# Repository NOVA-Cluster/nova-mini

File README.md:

# Nova Mini Project Suite

## Overview
The Nova Mini project suite consists of two main components that work together to create an interactive memory game experience:

1. Nova Mini (Receiver)
2. Nova Mini Remote (Sender)

These devices communicate wirelessly using ESP-NOW protocol to create an engaging, interactive game experience based on the classic Simon memory game.

## Components

### Nova Mini (Receiver)
The main game controller that:
- Handles core game logic and state management
- Controls LED patterns and audio feedback
- Processes player inputs
- Manages game progression through levels and rounds
- Provides hardware-level control and feedback

### Nova Mini Remote (Sender)
The user interface controller that:
- Initiates game commands and controls
- Sends instructions to the Nova Mini receiver
- Provides real-time game state updates
- Offers enhanced game mode features
- Enables remote gameplay control

## Technical Stack

### Hardware
Both devices are built on the ESP32 platform, featuring:
- ESP32 microcontroller
- LED indicators for visual feedback
- Push buttons for user input
- Buzzer for audio feedback
- Custom PCB design

### Software
Built using modern embedded development tools and frameworks:
- PlatformIO development environment
- Arduino framework for ESP32
- ESP-NOW protocol for wireless communication
- Custom libraries:
  - ESPUI for web interface
  - AsyncWebServer for configuration
  - MIDI Library for audio control
  - ArduinoJson for data serialization
  - OneButton for enhanced button control

## Communication

The devices use ESP-NOW, a connectionless wireless communication protocol that enables:
- Low-latency communication
- Peer-to-peer data exchange
- Efficient power usage
- Reliable message delivery

## Game Features

- Multiple difficulty levels and progressive rounds
- Real-time LED and audio feedback
- Enhanced state management with stages:
  - Sequence Generation
  - Input Collection
  - Verification
  - Round Transition
  - Game Win/Loss states
- Remote control capabilities
- Cheat mode for testing

## Setup and Configuration

The system includes a web-based configuration interface that allows:
- ESP-NOW pairing between devices
- MAC address management
- Game mode settings
- System preferences

## Development

This project is built using PlatformIO, offering:
- Cross-platform development
- Integrated dependency management
- Automated builds
- Extensive debugging capabilities
- Serial monitoring at 921600 baud

## Project Structure
```
nova-mini/
├── nova-mini (receiver)/        # Main game controller
│   ├── src/                    # Source files
│   ├── hardware/              # PCB and schematic files
│   └── platformio.ini         # Project configuration
└── nova-mini-remote (sender)/  # Remote controller
    ├── src/                    # Source files
    ├── docs/                   # Documentation
    ├── hardware/              # PCB and schematic files
    └── platformio.ini         # Project configuration
```

## Getting Started

1. Clone the repository
2. Open the project in PlatformIO
3. Install required dependencies
4. Configure the ESP-NOW settings through the web interface
5. Upload to respective devices
6. Access the web interface for additional configuration

## Building

Both projects use PlatformIO for building and deployment. Key build flags include:
- Thread name support
- ESP32 exception decoding
- Web server integration
- MIDI capabilities
- Custom debugging options

## Documentation

Detailed documentation is available in the `docs/` directory, including:
- ESP-NOW configuration guide
- Relationship between devices
- Hardware schematics
- PCB design files

## License

[Insert License Information]

## Contributing

[Insert Contribution Guidelines]

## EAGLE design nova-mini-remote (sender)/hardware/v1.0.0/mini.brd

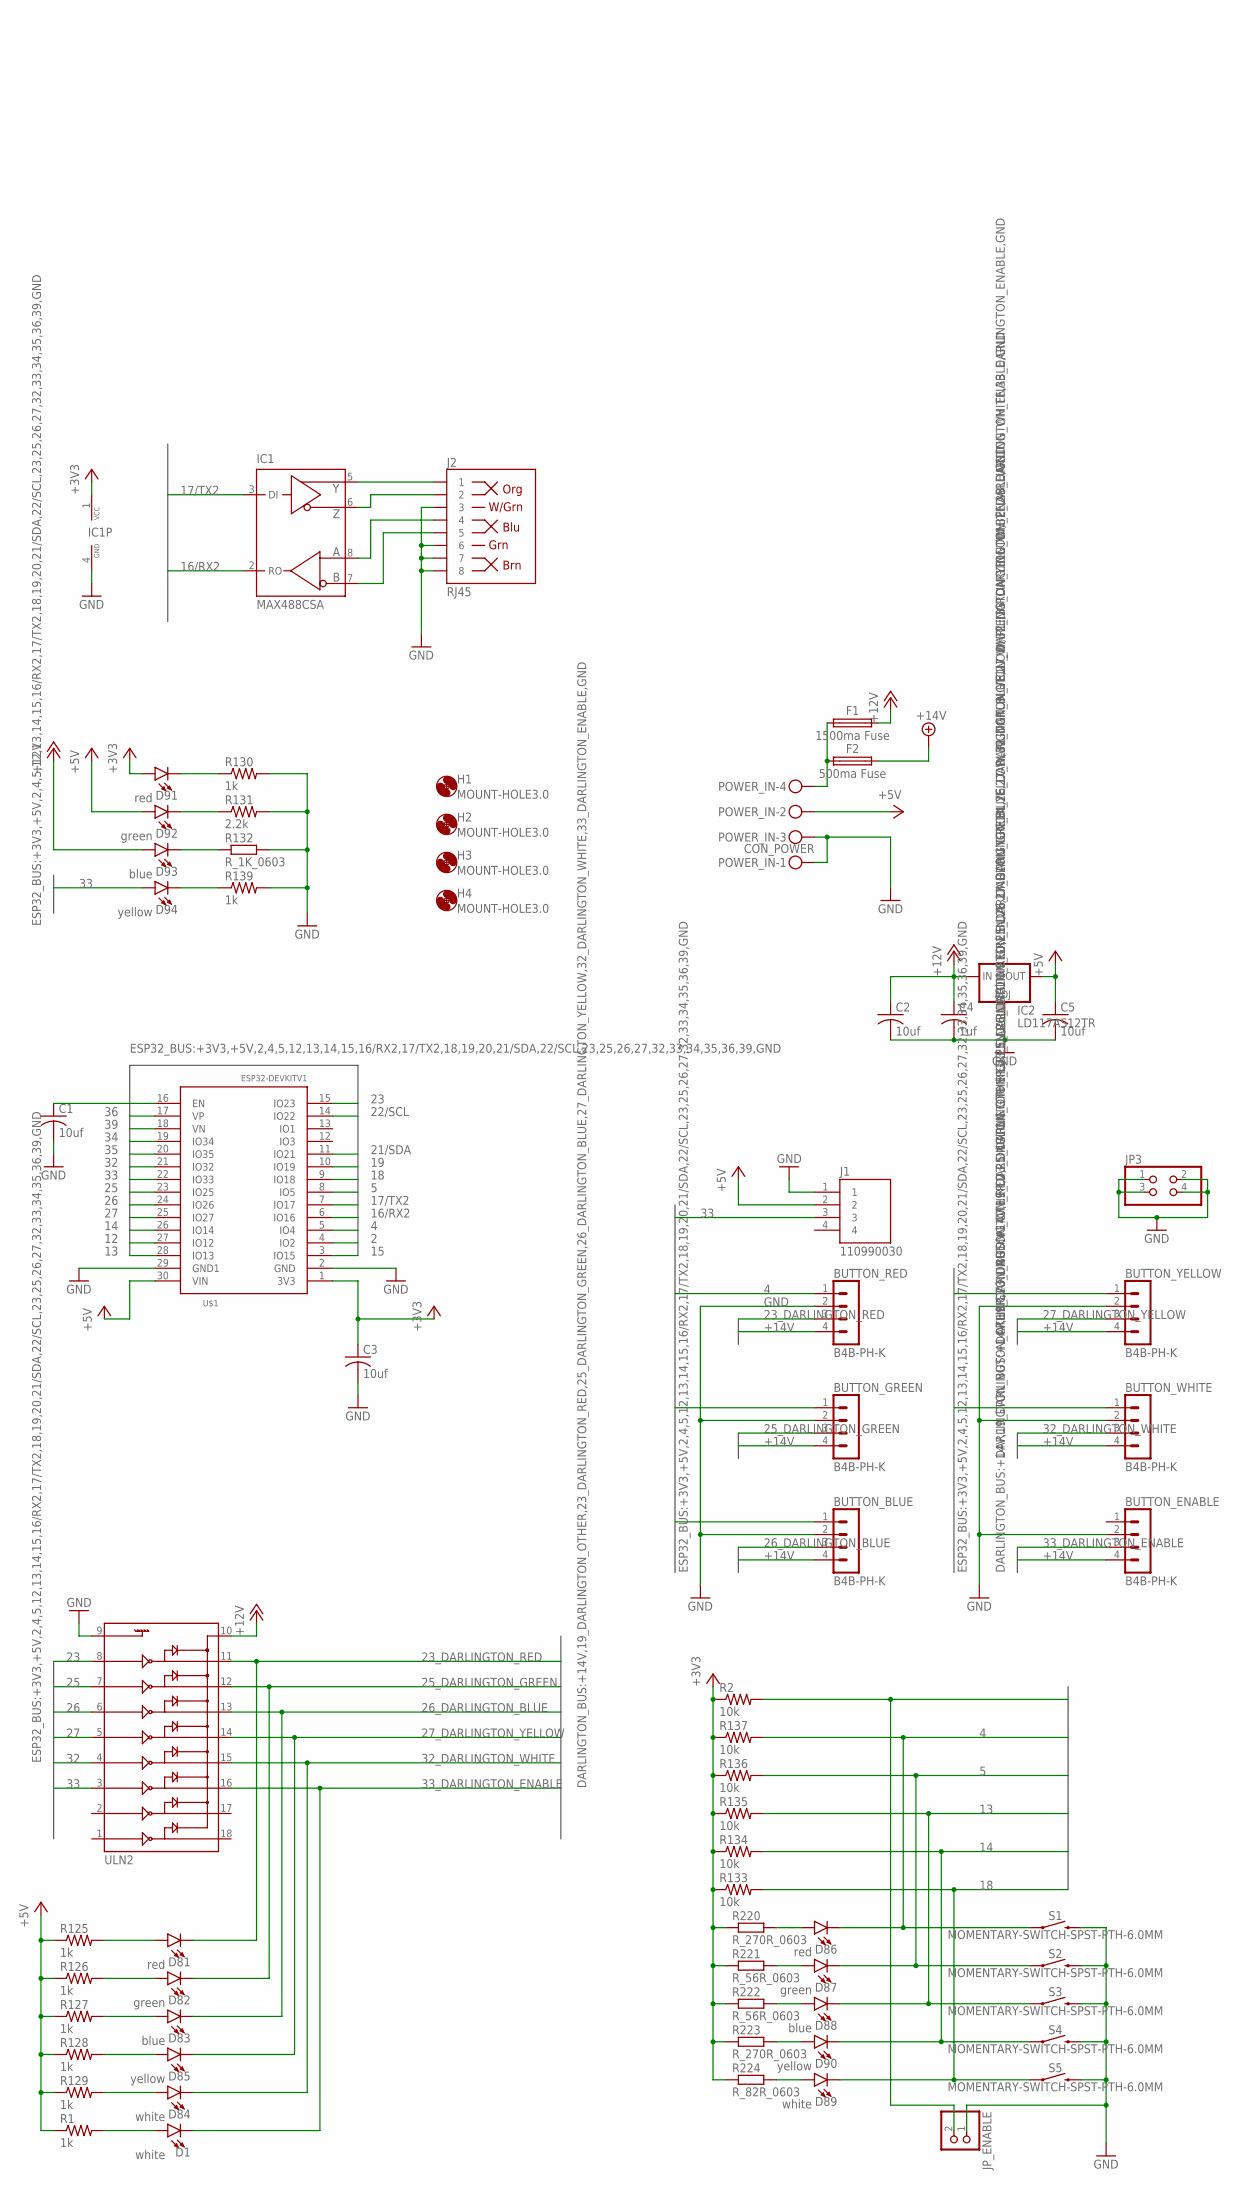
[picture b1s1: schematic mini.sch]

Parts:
BUTTON_BLUE: B4B-PH-K
BUTTON_ENABLE: B4B-PH-K
BUTTON_GREEN: B4B-PH-K
BUTTON_RED: B4B-PH-K
BUTTON_WHITE: B4B-PH-K
BUTTON_YELLOW: B4B-PH-K
C1, C2, C3, C5: 10uf; C0603; LCSC_PART C19702
C4: 1uf; C0805; LCSC_PART C15849
D1, D84, D89: white; LED-0603; LCSC_PART C2290
D81, D86, D91: red; LED-0603; LCSC_PART C2286
D82, D87, D92: green; LED-0603; LCSC_PART C72043
D83, D88, D93: blue; LED-0603; LCSC_PART C72041
D85, D90, D94: yellow; LED-0603; LCSC_PART C72038
F1: 1500ma Fuse; FUSC4632X160; LCSC_PART C78695
F2: 500ma Fuse; FUSC4632X160; LCSC_PART C70113
H1, H2, H3, H4: MOUNT-HOLE3.0; 3,0
IC1: MAX488CSA; SO08; LCSC_PART C179693
IC2: LD117AS12TR; SOT223; LCSC_PART C6187
J1: 110990030; SEEED_110990030
J2: RJ45; RJ45-8
JP3: PINHD-2X2; 2X02
JP_ENABLE: PINHD-1X2; 1X02
POWER_IN: CON_POWER; MKDSN1,5/4-5,08
R1, R125, R126, R127, R128, R129, R130, R139: 1k; R0603; LCSC_PART C21190
R2, R133, R134, R135, R136, R137: 10k; R0603; LCSC_PART C25804
R131: 2.2k; R0603; LCSC_PART C4190
R132: R_1K_0603; R0603
R220, R223: R_270R_0603; R0603
R221, R222: R_56R_0603; R0603
R224: R_82R_0603; R0603
S1, S2, S3, S4, S5: MOMENTARY-SWITCH-SPST-PTH-6.0MM; TACTILE_SWITCH_PTH_6.0MM
U$1: ESP32DEVKITV1; ESP32-DEVKITV1
ULN2: ULN2803SOICW; SO18L

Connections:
2: U$1.4 (IO2)
4: BUTTON_RED.1, D86.C, R137.2, S1.1, U$1.5 (IO4)
5: BUTTON_GREEN.1, D87.C, R136.2, S2.1, U$1.8 (IO5)
12: U$1.27 (IO12)
13: BUTTON_BLUE.1, D88.C, R135.2, S3.1, U$1.28 (IO13)
14: BUTTON_YELLOW.1, D90.C, R134.2, S4.1, U$1.26 (IO14)
15: U$1.3 (IO15)
16/RX2: IC1.2 (RO), U$1.6 (IO16)
17/TX2: IC1.3 (DI), U$1.7 (IO17)
18: BUTTON_WHITE.1, D89.C, R133.2, S5.1, U$1.9 (IO18)
19: JP_ENABLE.2, R2.2, U$1.10 (IO19)
21/SDA: U$1.11 (IO21)
22/SCL: U$1.14 (IO22)
23: U$1.15 (IO23), ULN2.8
23_DARLINGTON_RED: BUTTON_RED.3, D81.C, ULN2.11
25: U$1.23 (IO25), ULN2.7
25_DARLINGTON_GREEN: BUTTON_GREEN.3, D82.C, ULN2.12
26: U$1.24 (IO26), ULN2.6
26_DARLINGTON_BLUE: BUTTON_BLUE.3, D83.C, ULN2.13
27: U$1.25 (IO27), ULN2.5
27_DARLINGTON_YELLOW: BUTTON_YELLOW.3, D85.C, ULN2.14
32: U$1.21 (IO32), ULN2.4
32_DARLINGTON_WHITE: BUTTON_WHITE.3, D84.C, ULN2.15
33: D94.A, J1.3, U$1.22 (IO33), ULN2.3
33_DARLINGTON_ENABLE: BUTTON_ENABLE.3, D1.C, ULN2.16
34: U$1.19 (IO34)
35: U$1.20 (IO35)
36: U$1.17 (VP)
39: U$1.18 (VN)
+3V3: C3.1, D91.A, IC1.1 (VCC), R2.1, R133.1, R134.1, R135.1, R136.1, R137.1, R220.1, R221.1, R222.1, R223.1, R224.1, U$1.1 (3V3)
+5V: C5.1, D92.A, IC2.4 (OUT), J1.2, POWER_IN.2, R1.1, R125.1, R126.1, R127.1, R128.1, R129.1, U$1.30 (VIN)
+12V: C2.1, C4.1, D93.A, F1.2, IC2.3 (IN), ULN2.10
+14V: BUTTON_BLUE.4, BUTTON_ENABLE.4, BUTTON_GREEN.4, BUTTON_RED.4, BUTTON_WHITE.4, BUTTON_YELLOW.4, F2.2
GND: BUTTON_BLUE.2, BUTTON_ENABLE.2, BUTTON_GREEN.2, BUTTON_RED.2, BUTTON_WHITE.2, BUTTON_YELLOW.2, C1.2, C2.2, C3.2, C4.2, C5.2, IC1.4 (GND), IC2.1 (ADJ), J1.1, J2.3, J2.6, J2.7, J2.8, JP3.1, JP3.2, JP3.3, JP3.4, JP_ENABLE.1, POWER_IN.1, POWER_IN.3, R130.2, R131.2, R132.2, R139.2, S1.3 (2), S2.3 (2), S3.3 (2), S4.3 (2), S5.3 (2), U$1.2 (GND), U$1.29 (GND1), ULN2.9
unnamed: C1.1, U$1.16 (EN)
unnamed: D1.A, R1.2
unnamed: IC1.5 (Y), J2.1
unnamed: IC1.6 (Z), J2.2
unnamed: IC1.8 (A), J2.4
unnamed: IC1.7 (B), J2.5
unnamed: D84.A, R129.2
unnamed: D85.A, R128.2
unnamed: D83.A, R127.2
unnamed: D82.A, R126.2
unnamed: D81.A, R125.2
unnamed: D91.C, R130.1
unnamed: D92.C, R131.1
unnamed: D93.C, R132.1
unnamed: D94.C, R139.1
unnamed: D86.A, R220.2
unnamed: D87.A, R221.2
unnamed: D88.A, R222.2
unnamed: D90.A, R223.2
unnamed: D89.A, R224.2
unnamed: F1.1, F2.1, POWER_IN.4

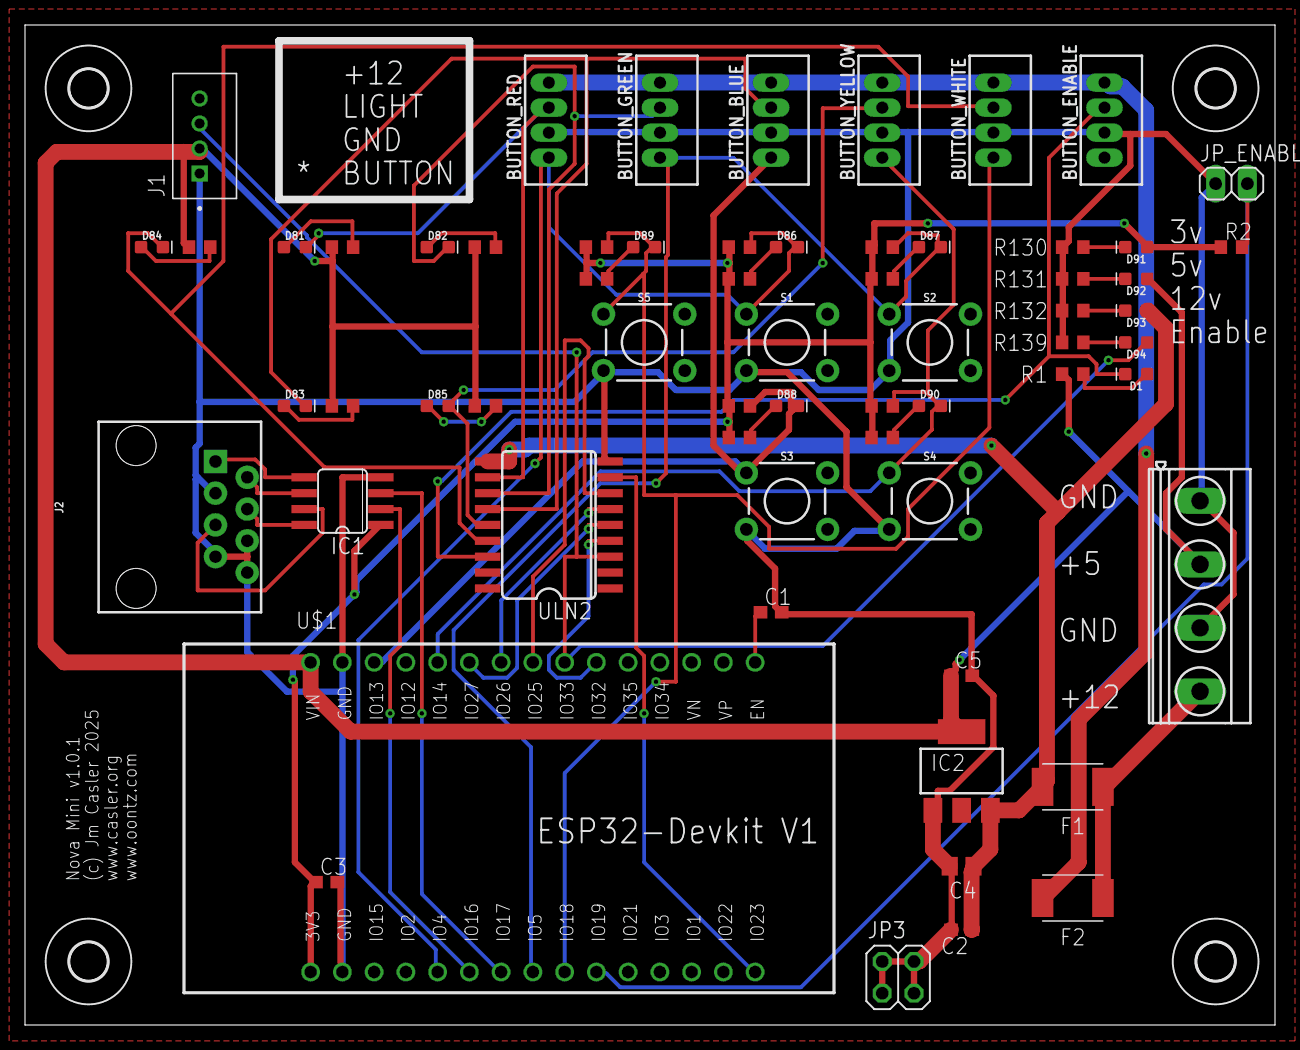
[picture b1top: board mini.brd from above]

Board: 2 copper layers, 100.0 x 80.0 mm, 67 parts (0 on the bottom side), 46 nets.

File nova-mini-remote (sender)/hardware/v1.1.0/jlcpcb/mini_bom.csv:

Comment,Designator,Footprint,LCSC Part #
,JP_ENABLE,1X02,
,JP3,2X02,
,ULN2,SO18L,C9683
1k,R1 R125 R126 R127 R128 R129 R130 R139,R0603,C21190
1uf,C4,C0805,C15849
2.2k,R131,R0603,C4190
10k,R2 R133 R134 R135 R136 R137,R0603,C25804
10uf,C1 C2 C3 C5,C0603,C19702
500ma Fuse,F2,FUSC4632X160,C70113
1500ma Fuse,F1,FUSC4632X160,C78695
110990030,J1,SEEED_110990030,
B4B-PH-K,BUTTON_BLUE BUTTON_ENABLE BUTTON_GREEN BUTTON_RED BUTTON_WHITE BUTTON_YELLOW,B4B-PH-K,
CON_POWER,POWER_IN,MKDSN1 5/4-5 08,
ESP32DEVKITV1,U$1,ESP32-DEVKITV1,
LD117AS12TR,IC2,SOT223,C6187
MAX488CSA,IC1,SO08,C179693
MOMENTARY-SWITCH-SPST-PTH-6.0MM,S1 S2 S3 S4 S5,TACTILE_SWITCH_PTH_6.0MM,
RJ45,J2,RJ45-8,
R_1K_0603,R132,R0603,C21190
R_56R_0603,R221 R222,R0603,C25196
R_82R_0603,R224,R0603,C23255
R_270R_0603,R220 R223,R0603,C22966
blue,D83 D88 D93,LED-0603,C72041
green,D82 D87 D92,LED-0603,C72043
red,D81 D86 D91,LED-0603,C2286
white,D1 D84 D89,LED-0603,C2290
yellow,D85 D90 D94,LED-0603,C72038

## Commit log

2024-12-28 Switch to esp32s3box
2024-12-28 refactor relay control and begin adding threading
2025-01-28 stuff
2025-02-09 Web control of the poofers
2025-02-09 add a few more relay functions
2025-02-09 Refinement of web interface
2025-02-09 initial of espnow
2025-02-15 change monitor speed.
2025-02-15 implement new SimonaMessage structure
2025-02-15 call simonaDisplay from the protocol handler
2025-02-15 move safeSerialPrint into utilities.
2025-02-15 add more comments.
2025-02-15 move pin defines to configuration
2025-02-16 Improve ack, show logo, improve debug
2025-02-16 minor cleanup
2025-02-16 Update novalogo to take less space in flash.
2025-02-20 Add support for the output LEDs
2025-02-20 Place holder sequences and create displaySimonaStageInputCollectionAnimation
2025-02-20 new game lost and game reset animations
2025-02-20 New win animation
2025-02-21 stage sequence animation (not done)
2025-02-21 it all works!
2025-02-21 add relay control to sequence generation, input and win
2025-02-26 Cleanup web, fix web loop in tasks, fix mac address
2025-02-27 use the last of mac from the remote
2025-02-27 update pulse
2025-02-27 add rounds information
2025-02-27 Add peer pairing
2025-02-28 Restructuring
2025-03-01 change the round sequence animation to 5
2025-03-01 Add packet loss counter
2025-03-01 change wifi status print to once every 30 seconds
2025-03-01 Messages in the last 5 minutes was not accurate, fixed
2025-03-01 Wireless enable and game enable toggle
2025-03-01 Factory reset and status updates
2025-03-01 update cheat mode status text
2025-03-01 small refactoring of sender config
2025-03-01 added round animation
2025-03-01 fix stage lookup
2025-03-01 minor changes
2025-03-01 Add round animation
2025-03-01 Refactor to use the preferences manager from the sender
2025-03-01 Factory reset, poofer enable switch, device stats
2025-03-01 Update dump slider
2025-03-01 move some things around
2025-03-01 fix connectedRemotes bug
2025-03-01 mechanism to detect when a peer is disconnected
2025-03-01 autoformat
2025-03-01 Refactoring and moving things into folders
2025-03-03 comment out unused methods
2025-03-03 use thread safe delays
2025-03-03 Update poofer output to 25ms
2025-03-03 Invert led output states
2025-03-03 start with the buttons on and dim when a button is pushed.
2025-03-03 set dim
2025-03-03 Added comments
2025-03-03 Fixed led <-> relay mapping
2025-03-03 Fix led / relay mapping
2025-03-03 Local echo preference/web toggle
2025-03-06 Refactored preferencesmanager
    Will use this on Nova as well.
2025-03-07 moved setLedBrightness
2025-03-09 Remove unused library
2025-03-09 Bump arduinojson
2025-03-09 Update RMT library to code ticks
2025-03-09 Change name of button constants
2025-03-11 Revert "Change name of button constants"
    This reverts commit e887426c8f1fb3a70d76e88bdc107bca3ef324e2.
2025-03-12 Fix problem with RMT and add readme
2025-04-16 Upgrade libraries
2025-04-16 Add estop
2025-04-16 estop status on web interface
2025-04-16 add estop task
2025-04-16 Don't send network if estop
2025-04-16 Add estop config
2025-04-16 Move espnow loop to a task
2025-04-16 Refactor tasks and add wifimulti
2025-04-23 Remove wifi multi. causes problems with espnow
2025-05-03 verificationAnimation Sequence created
2025-07-20 Add debug print for input collection stage
    Inserted a Serial.println statement to indicate when SIMONA_STAGE_INPUT_COLLECTION is entered, aiding in debugging and stage tracking.
2025-07-20 Track message_id for input collection animations
    Introduces currentLastPressedMessageId to track the last message_id during INPUT_COLLECTION stage, enabling more precise relay and LED animation timing. Updates SimonaDisplay, SimonaDisplaySequences,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

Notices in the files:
parts and their libraries:
SparkFun-LED: Licensing: Creative Commons ShareAlike 4.0 International - https://creativecommons.org/licenses/by-sa/4.0
con-jst-ph: Copyright (C) 2016, Bob Starr
